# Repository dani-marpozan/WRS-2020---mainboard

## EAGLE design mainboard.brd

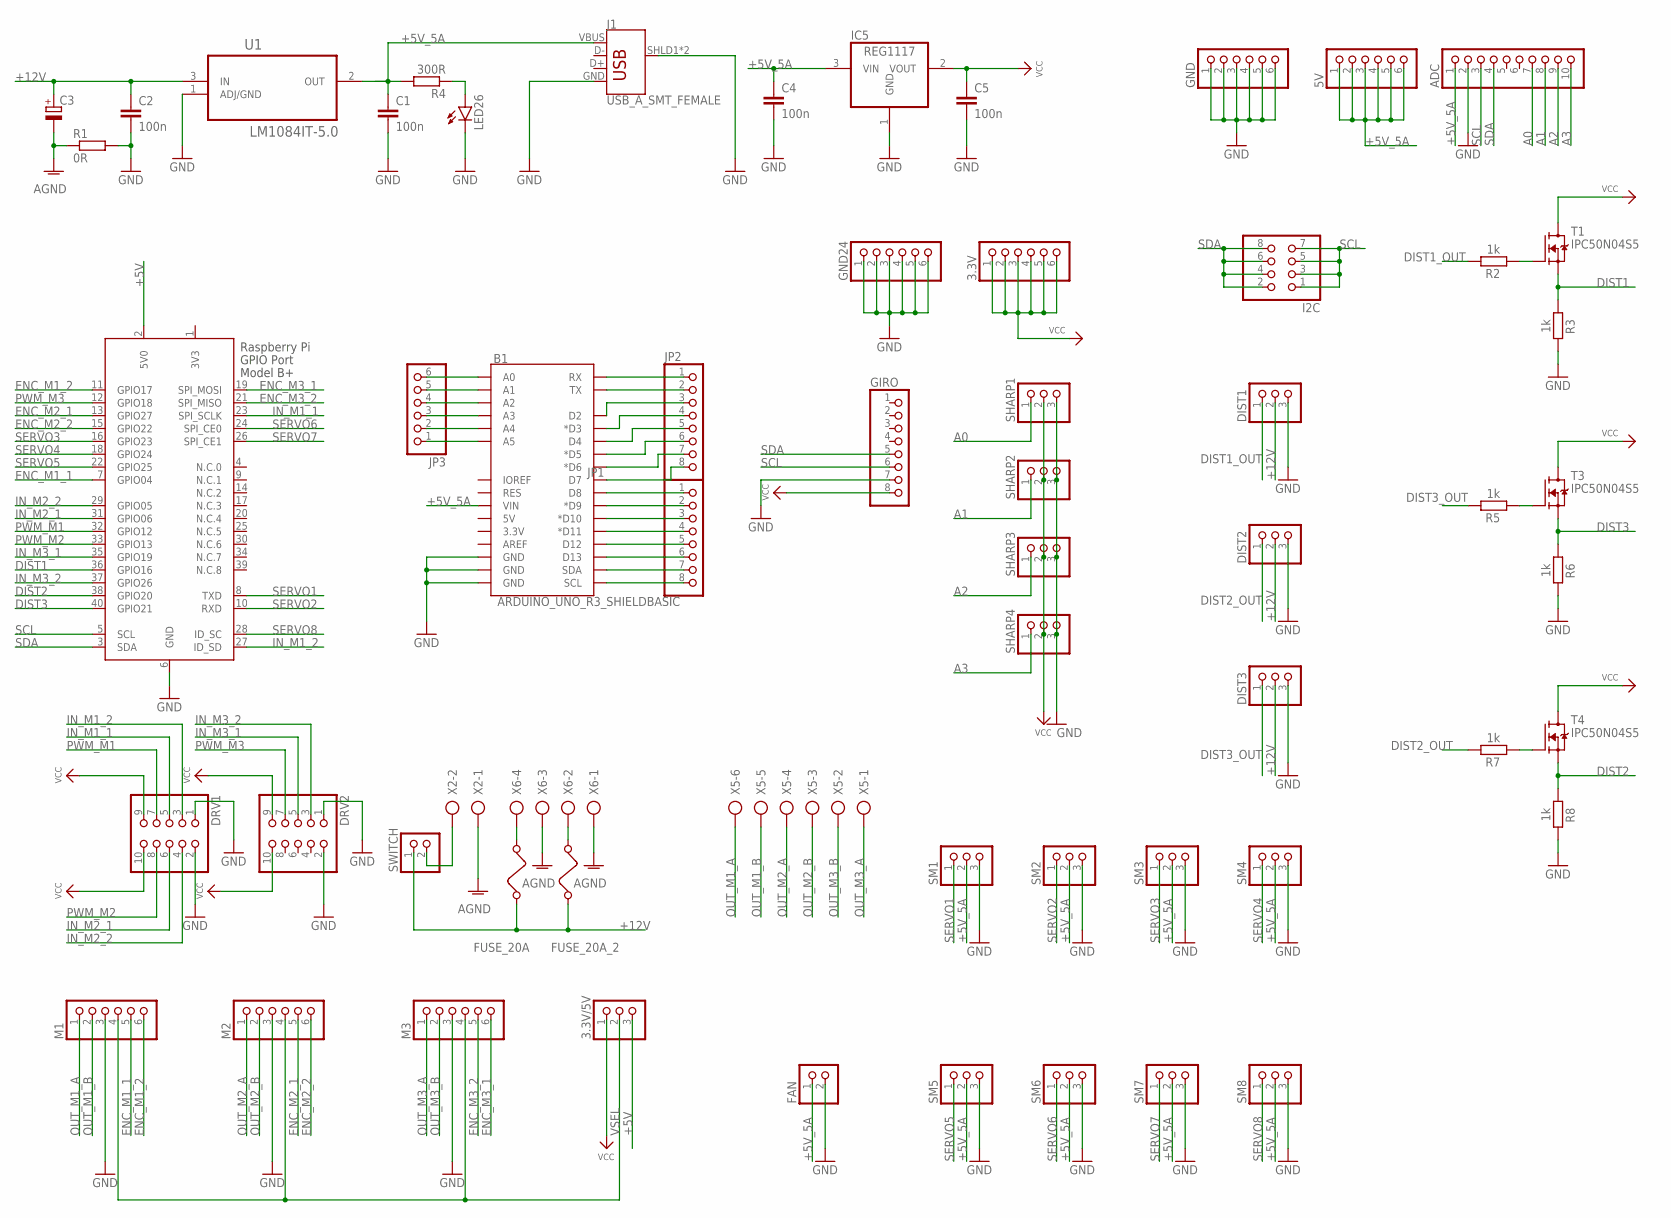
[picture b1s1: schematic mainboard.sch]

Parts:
3.3V, 5V: PINHD-1X6; 1X06
3.3V/5V: PINHD-1X3; 1X03
ADC: PINHD-1X10; 1X10
B1: ARDUINO_UNO_R3_SHIELDBASIC; UNO_R3_SHIELD
C1, C2, C4, C5: 100n; C0805
C3: UCD1V221MNL1GS; CAPAE830X1050
DIST1, DIST2, DIST3: PINHD-1X3; 1X03
DRV1, DRV2: PINHD-2X5; 2X05
FAN: PINHD-1X2; 1X02
FUSE_20A, FUSE_20A_2: FUSE
GIRO: PINHD-1X8; 1X08
GND, GND24: PINHD-1X6; 1X06
I2C: PINHD-2X4; 2X04
IC5: REG1117; SOT223
J1: USB_A_SMT_FEMALE; USB-A-S-SILK-FEMALE
JP1, JP2: PINHD-1X8; 1X08
JP3: PINHD-1X6; 1X06
LED26: LEDCHIP-LED0805; CHIP-LED0805
M1, M2, M3: PINHD-1X6; 1X06
R1: 0R; M0805
R2, R3, R5, R6, R7, R8: 1k; R0805
R4: 300R; R0805
SHARP1, SHARP2, SHARP3, SHARP4: PINHD-1X3; 1X03
SM1, SM2, SM3, SM4, SM5, SM6, SM7, SM8: PINHD-1X3; 1X03
SWITCH: PINHD-1X2; 1X02
T1, T3, T4: IPC50N04S5; PG-TDSON-8-33
U1: LM1084IT-5.0; TO254P470X1016X2222-3P
X1: RASPI_BOARD_B+_FP; RASPI_BOARD_B+_FULL_PAD
X2: AK500/2
X5: AK500/6
X6: AK500/4

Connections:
3V3: X1.1 (3V3)
+5V: 3.3V/5V.3, X1.2 (5V0)
+5V_5A: 5V.1, 5V.2, 5V.3, 5V.4, 5V.5, 5V.6, ADC.1, B1.VIN, C1.1, C4.1, FAN.1, IC5.3 (VIN), J1.VBUS, R4.2, SM1.2, SM2.2, SM3.2, SM4.2, SM5.2, SM6.2, SM7.2, SM8.2, U1.2 (OUT)
+12V: C2.1, C3.1 (+), DIST1.2, DIST2.2, DIST3.2, FUSE_20A.1, FUSE_20A_2.1, SWITCH.1, U1.3 (IN)
A0: ADC.7, SHARP1.1
A1: ADC.8, SHARP2.1
A2: ADC.9, SHARP3.1
A3: ADC.10, SHARP4.1
AGND: C3.2 (-), R1.1, X2.1, X6.1, X6.3
DIST1: R3.1, T1.2 (S), X1.36 (GPIO16)
DIST1_OUT: DIST1.1, R2.2
DIST2: R8.1, T4.2 (S), X1.38 (GPIO20)
DIST2_OUT: DIST2.1, R7.2
DIST3: R6.1, T3.2 (S), X1.40 (GPIO21)
DIST3_OUT: DIST3.1, R5.2
ENC_M1_1: M1.5, X1.7 (GPIO04)
ENC_M1_2: M1.6, X1.11 (GPIO17)
ENC_M2_1: M2.5, X1.13 (GPIO27)
ENC_M2_2: M2.6, X1.15 (GPIO22)
ENC_M3_1: M3.6, X1.19 (SPI_MOSI)
ENC_M3_2: M3.5, X1.21 (SPI_MISO)
GND: ADC.2, B1.GND@0 (GND), B1.GND@1 (GND), B1.GND@2 (GND), C1.2, C2.2, C4.2, C5.2, DIST1.3, DIST2.3, DIST3.3, DRV1.1, DRV1.2, DRV2.1, DRV2.2, FAN.2, GIRO.7, GND.1, GND.2, GND.3, GND.4, GND.5, GND.6, GND24.1, GND24.2, GND24.3, GND24.4, GND24.5, GND24.6, IC5.1 (GND), J1.GND, J1.SHLD1 (SHIELD), J1.SHLD2 (SHIELD), LED26.C, M1.3, M2.3, M3.3, R1.2, R3.2, R6.2, R8.2, SHARP1.3, SHARP2.3, SHARP3.3, SHARP4.3, SM1.3, SM2.3, SM3.3, SM4.3, SM5.3, SM6.3, SM7.3, SM8.3, U1.1 (ADJ/GND), X1.6 (GND)
IN_M1_1: DRV1.5, X1.23 (SPI_SCLK)
IN_M1_2: DRV1.3, X1.27 (ID_SD)
IN_M2_1: DRV1.6, X1.31 (GPIO06)
IN_M2_2: DRV1.4, X1.29 (GPIO05)
IN_M3_1: DRV2.5, X1.35 (GPIO19)
IN_M3_2: DRV2.3, X1.37 (GPIO26)
unnamed: FUSE_20A.2, X6.4
unnamed: FUSE_20A_2.2, X6.2
unnamed: SWITCH.2, X2.2
unnamed: LED26.A, R4.1
unnamed: B1.RX, JP2.1
unnamed: B1.D8, JP1.1
unnamed: B1.D9 (*D9), JP1.2
unnamed: B1.D10 (*D10), JP1.3
unnamed: B1.D11 (*D11), JP1.4
unnamed: B1.D12, JP1.5
unnamed: B1.D13, JP1.6
unnamed: B1.SDA, JP1.7
unnamed: B1.SCL, JP1.8
unnamed: B1.TX, JP2.2
unnamed: B1.D2, JP2.3
unnamed: B1.D3 (*D3), JP2.4
unnamed: B1.D4, JP2.5
unnamed: B1.D5 (*D5), JP2.6
unnamed: B1.D6 (*D6), JP2.7
unnamed: B1.D7, JP2.8
unnamed: B1.A0, JP3.6
unnamed: B1.A1, JP3.5
unnamed: B1.A2, JP3.4
unnamed: B1.A3, JP3.3
unnamed: B1.A4, JP3.2
unnamed: B1.A5, JP3.1
unnamed: R2.1, T1.3 (G)
unnamed: R5.1, T3.3 (G)
unnamed: R7.1, T4.3 (G)
OUT_M1_A: M1.1, X5.6
OUT_M1_B: M1.2, X5.5
OUT_M2_A: M2.1, X5.4
OUT_M2_B: M2.2, X5.3
OUT_M3_A: M3.1, X5.1
OUT_M3_B: M3.2, X5.2
PWM_M1: DRV1.7, X1.32 (GPIO12)
PWM_M2: DRV1.8, X1.33 (GPIO13)
PWM_M3: DRV2.7, X1.12 (GPIO18)
SCL: ADC.3, GIRO.6, I2C.1, I2C.3, I2C.5, I2C.7, X1.5 (SCL)
SDA: ADC.4, GIRO.5, I2C.2, I2C.4, I2C.6, I2C.8, X1.3 (SDA)
SERVO1: SM1.1, X1.8 (TXD)
SERVO2: SM2.1, X1.10 (RXD)
SERVO3: SM3.1, X1.16 (GPIO23)
SERVO4: SM4.1, X1.18 (GPIO24)
SERVO5: SM5.1, X1.22 (GPIO25)
SERVO6: SM6.1, X1.24 (SPI_CE0)
SERVO7: SM7.1, X1.26 (SPI_CE1)
SERVO8: SM8.1, X1.28 (ID_SC)
VCC: 3.3V.1, 3.3V.2, 3.3V.3, 3.3V.4, 3.3V.5, 3.3V.6, 3.3V/5V.1, C5.1, DRV1.9, DRV1.10, DRV2.9, DRV2.10, GIRO.8, IC5.2 (VOUT), SHARP1.2, SHARP2.2, SHARP3.2, SHARP4.2, T1.1 (D), T3.1 (D), T4.1 (D)
VSEL: 3.3V/5V.2, M1.4, M2.4, M3.4

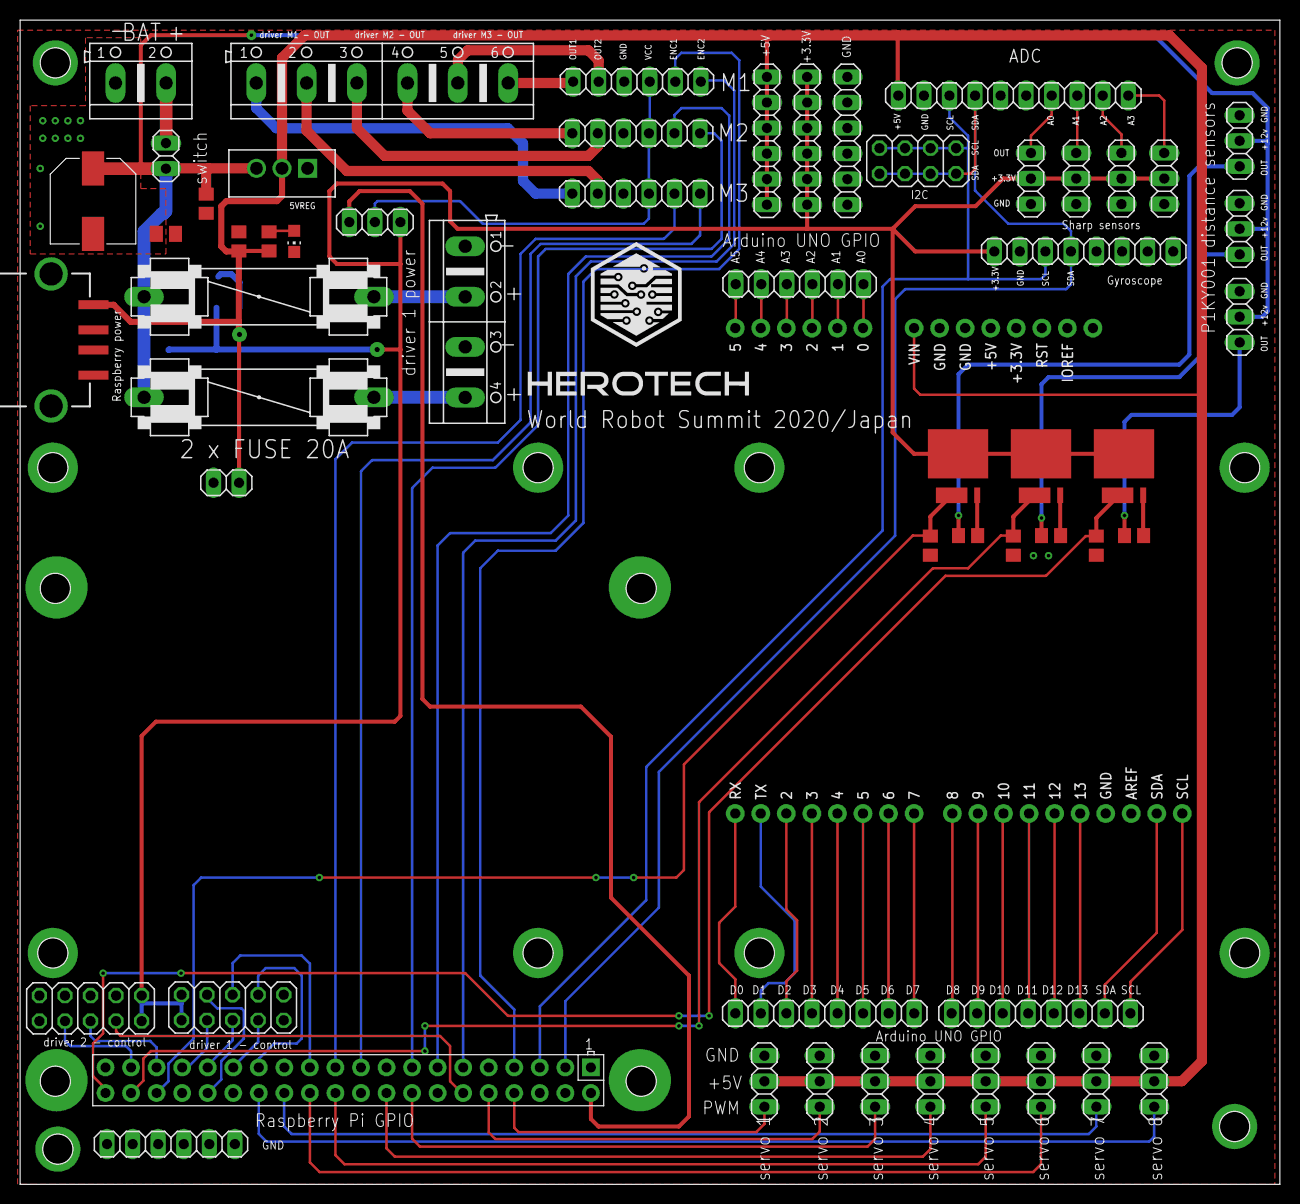
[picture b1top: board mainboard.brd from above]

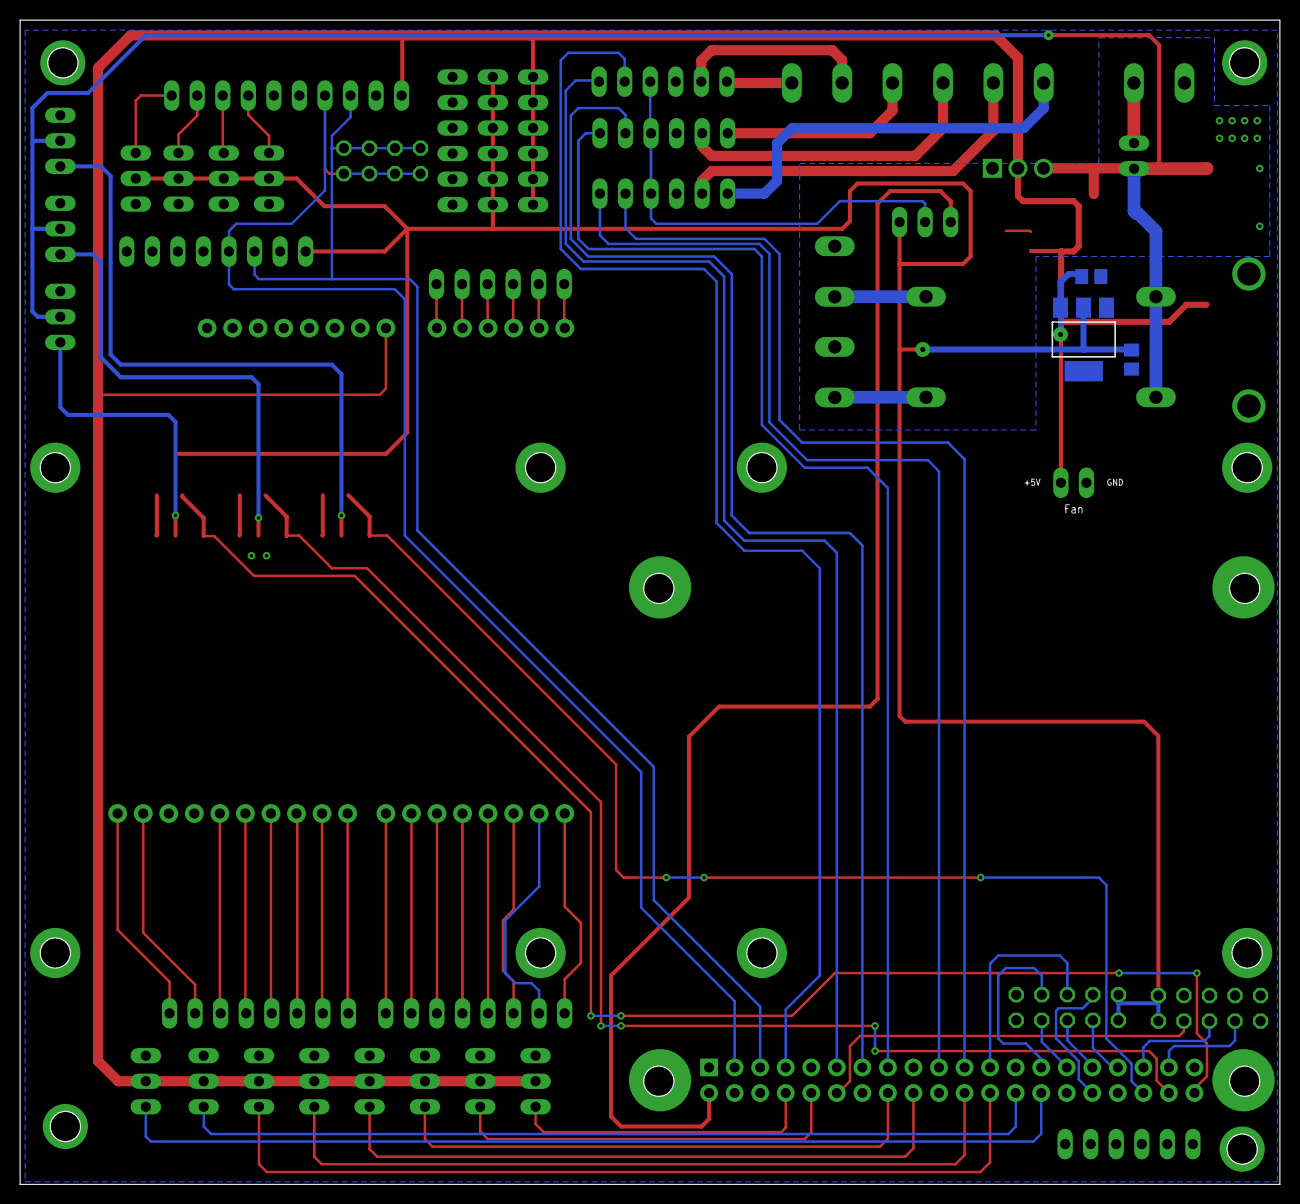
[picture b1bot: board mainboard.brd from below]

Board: 2 copper layers, 125.2 x 115.8 mm, 60 parts (3 on the bottom side), 77 nets.

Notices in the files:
parts and their libraries:
SparkFun-Connectors: Licensing: Creative Commons ShareAlike 4.0 International - https://creativecommons.org/licenses/by-sa/4.0
